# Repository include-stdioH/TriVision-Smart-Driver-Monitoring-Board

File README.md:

# TriVision-Smart-Driver-Monitoring-Board
ESP32-S3 based Smart Driver Monitoring Sensor Board designed in KiCad.
# TriVision – Smart Driver Monitoring Sensor Board

## Overview

TriVision is a custom-designed ESP32-S3-based sensor board developed for intelligent driver monitoring and vehicle safety applications. The board integrates biometric and motion sensing capabilities to detect driver fatigue, drowsiness, distraction, and abnormal driving conditions.

This project was designed using KiCad and includes complete schematic design, PCB layout, component placement, routing, and 3D visualization.

---

## Features

* ESP32-S3 based processing unit
* Heart-rate and SpO₂ monitoring using MAX30102
* Motion and orientation sensing using MPU6050
* Driver alert buzzer system
* Status indication LEDs
* USB Type-C power input
* On-board 3.3V regulation using AMS1117
* Compact custom PCB design
* Ready for IoT and AI-based driver monitoring applications

---

## Hardware Components

| Component        | Function                    |
| ---------------- | --------------------------- |
| ESP32-S3-WROOM-1 | Main microcontroller        |
| MAX30102         | Heart-rate and SpO₂ sensor  |
| MPU6050          | Accelerometer and gyroscope |
| AMS1117-3.3      | Voltage regulator           |
| USB Type-C       | Power input                 |
| Buzzer           | Driver warning alerts       |
| LEDs             | System status indication    |

---

## System Architecture

USB-C Power Input → AMS1117 → 3.3V Rail

ESP32-S3 ↔ MAX30102 (I²C)

ESP32-S3 ↔ MPU6050 (I²C)

ESP32-S3 → Buzzer

ESP32-S3 → Status LEDs

---

## PCB Design Highlights

* Two-layer PCB
* ESP32 antenna keep-out region implemented
* Dedicated 3.3V power distribution
* Decoupling capacitors placed near critical devices
* I²C pull-up resistors included
* Designed following standard PCB layout practices

---

## Design Tools

* KiCad 10
* GitHub

---

## Future Improvements

* Camera-based drowsiness detection
* CAN Bus integration
* Vehicle telemetry support
* Edge AI processing
* Mobile application integration

---

## Author

Anushri Logesh

Electronics and Communication Engineering

Embedded Systems & AI Enthusiast

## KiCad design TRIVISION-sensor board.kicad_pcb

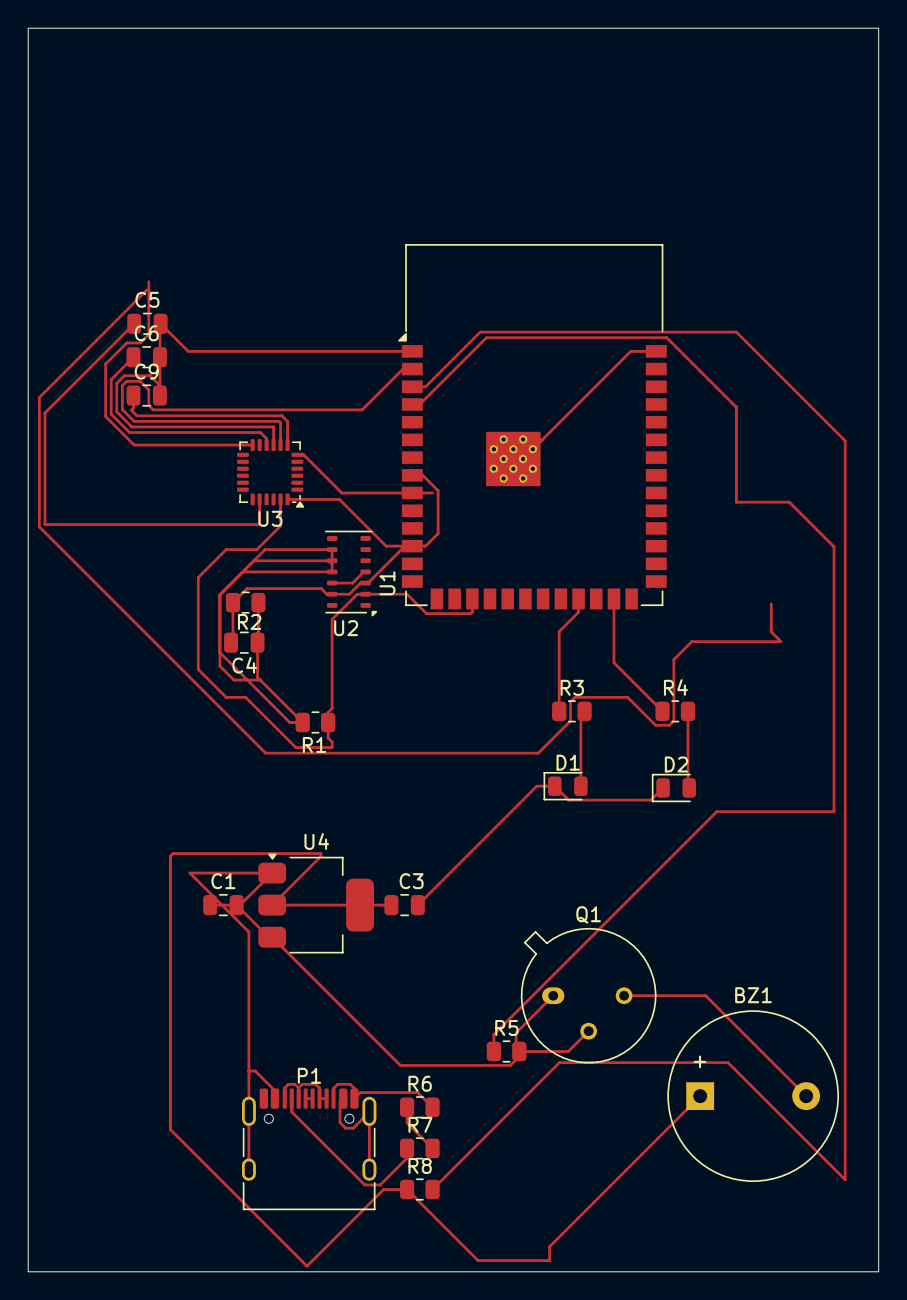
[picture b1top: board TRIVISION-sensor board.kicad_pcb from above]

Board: 2 copper layers, 61.0 x 89.2 mm, 23 parts (0 on the bottom side), 19 nets.

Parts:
BZ1: Buzzer; Buzzer_12x9.5RM7.6
C1, C3: 10u; C_0805_2012Metric
C4, C5, C6, C9: 100n; C_0805_2012Metric
D1: GREEN; LED_0805_2012Metric
D2: RED; LED_0805_2012Metric
P1: USB_C_Plug_USB2.0; USB_C_Receptacle_HRO_TYPE-C-31-M-12
Q1: 2N2219; TO-39-3
R1, R2: 4.7K; R_0805_2012Metric
R3, R4: 330; R_0805_2012Metric
R5: 1K; R_0805_2012Metric
R6, R7: 5.1K; R_0805_2012Metric
R8: 10K; R_0805_2012Metric
U1: ESP32-S3-WROOM-1
U2: MAX30102; Maxim_OLGA-14_3.3x5.6mm_P0.8mm
U3: MPU-6050; InvenSense_QFN-24_4x4mm_P0.5mm
U4: AMS1117; SOT-223-3_TabPin2

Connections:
+3.3V: BZ1.1 (+), C3.1, C4.1, R1.2, R2.1, R8.1, U1.2 (3V3), U2.9 (VLED+), U2.10 (VLED+), U2.11 (VDD), U3.8 (VLOGIC), U3.13 (VDD), U4.2 (VO)
Earth: P1.A1 (GND), P1.A6 (D+), P1.A7 (D-), P1.A12 (GND), P1.B1 (GND), P1.B5 (VCONN), P1.B12 (GND), R6.2
GND: C1.1, C1.2, C3.2, C5.2, C6.2, C9.2, D1.1 (K), D2.1 (K), P1.A4 (VBUS), P1.A9 (VBUS), P1.B4 (VBUS), P1.B9 (VBUS), P1.SH (SHIELD), Q1.1 (E), U1.1 (GND), U1.40 (GND), U1.41 (GND), U2.4 (PGND), U2.12 (GND), U3.9 (AD0), U3.11 (FSYNC), U3.18 (GND), U4.1 (ADJ), U4.3 (VI)
unnamed: BZ1.2 (-), Q1.3 (C)
unnamed: D1.2 (A), R3.2
unnamed: D2.2 (A), R4.2
unnamed: P1.A5 (CC), R7.1
unnamed: Q1.2 (B), R5.2
unnamed: R6.1, R7.2
unnamed: R8.2, U1.3 (EN)
unnamed: R5.1, U1.4 (IO4)
unnamed: R1.1, U1.17 (IO9), U2.2 (SCL), U3.23 (SCL)
unnamed: C4.2, R2.2, U1.8 (IO15), U1.12 (IO8), U2.3 (SDA), U2.13 (~INT), U3.24 (SDA)
unnamed: U1.9 (IO16), U3.6 (AUX_DA), U3.12 (INT)
unnamed: R3.1, U1.23 (IO21)
unnamed: R4.1, U1.25 (IO48)
unnamed: C9.1, U3.7 (AUX_CL)
unnamed: C5.1, U3.20 (CPOUT)
unnamed: C6.1, U3.10 (REGOUT)
